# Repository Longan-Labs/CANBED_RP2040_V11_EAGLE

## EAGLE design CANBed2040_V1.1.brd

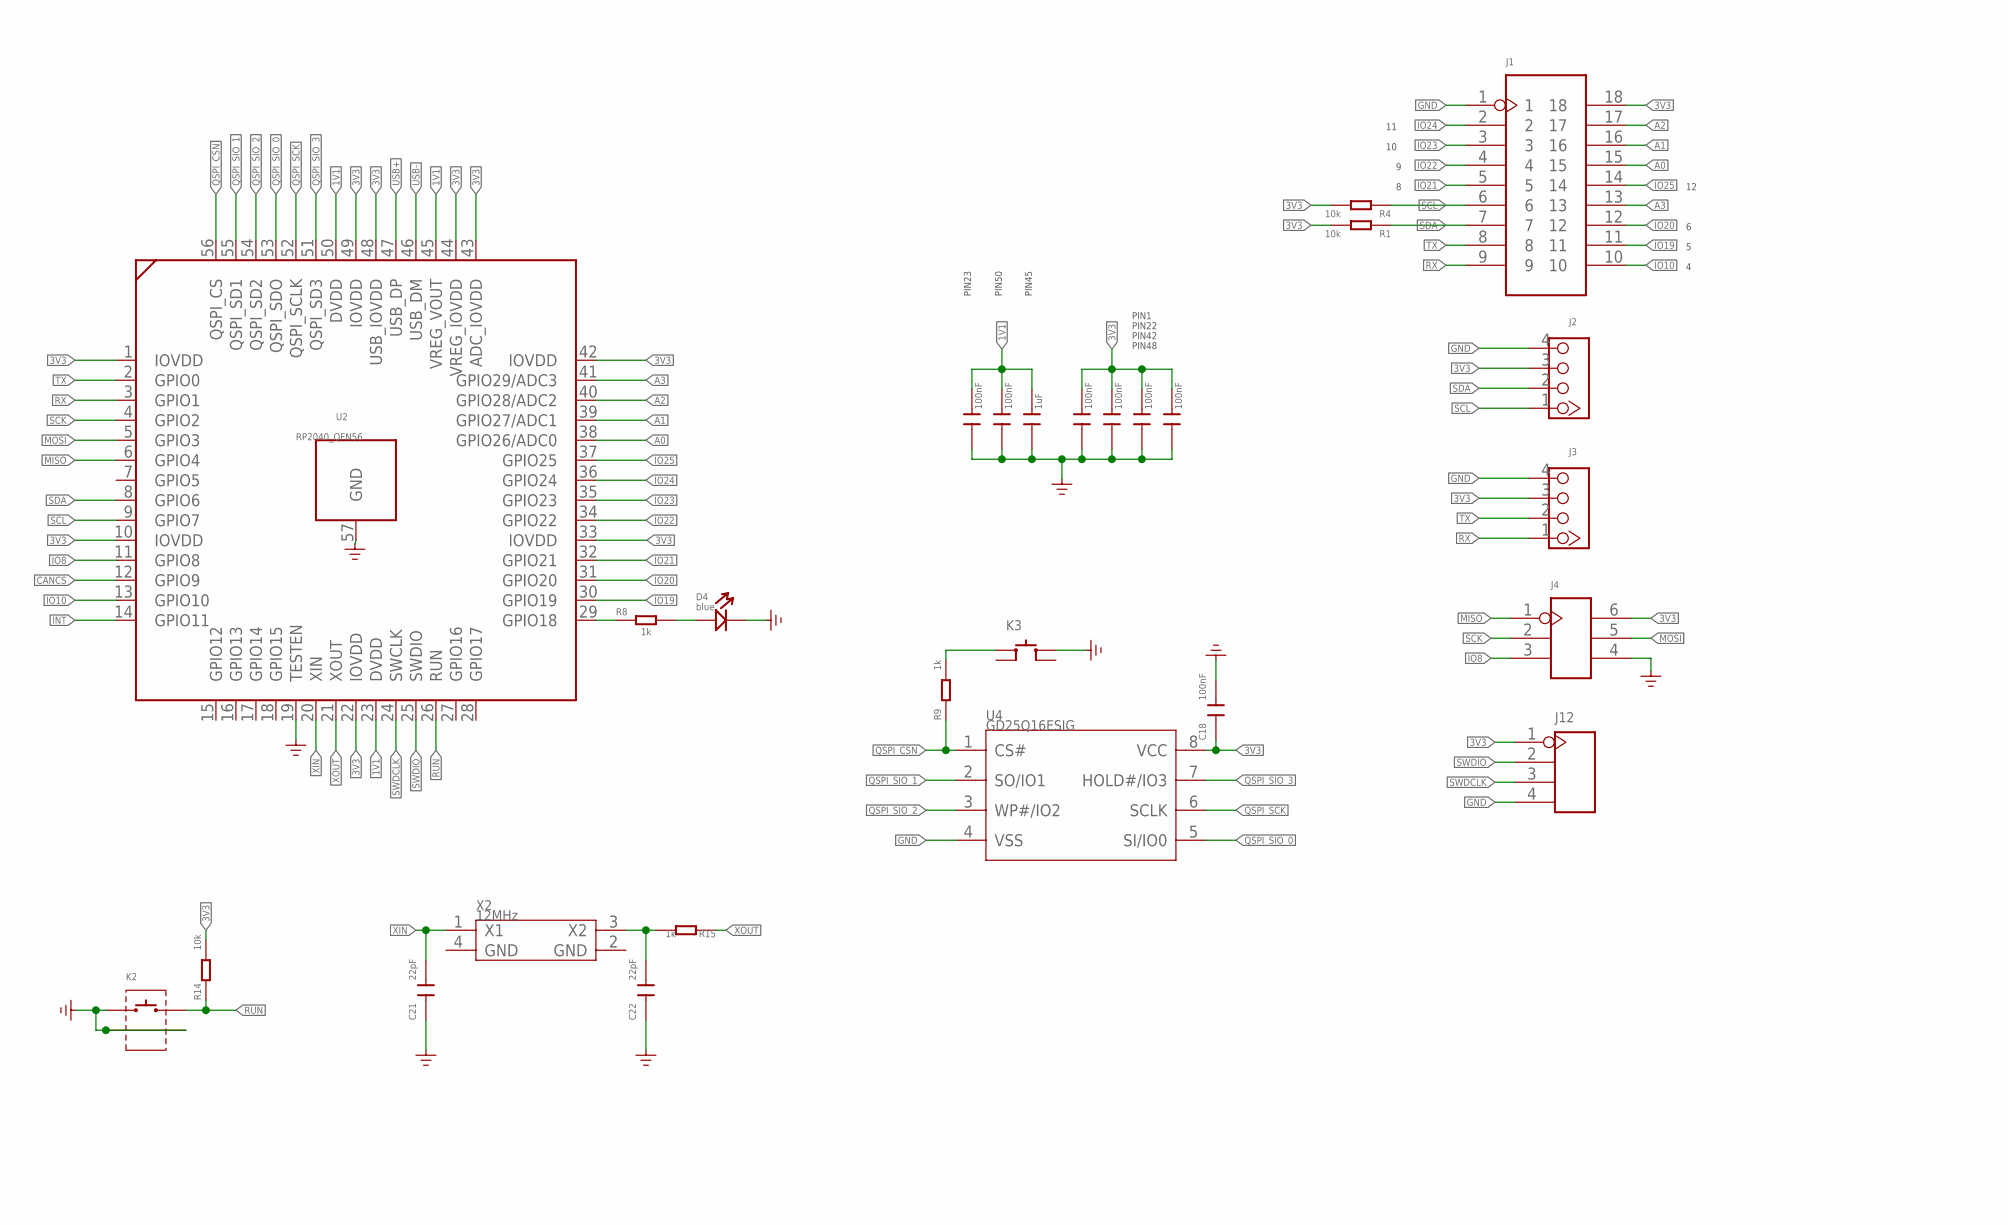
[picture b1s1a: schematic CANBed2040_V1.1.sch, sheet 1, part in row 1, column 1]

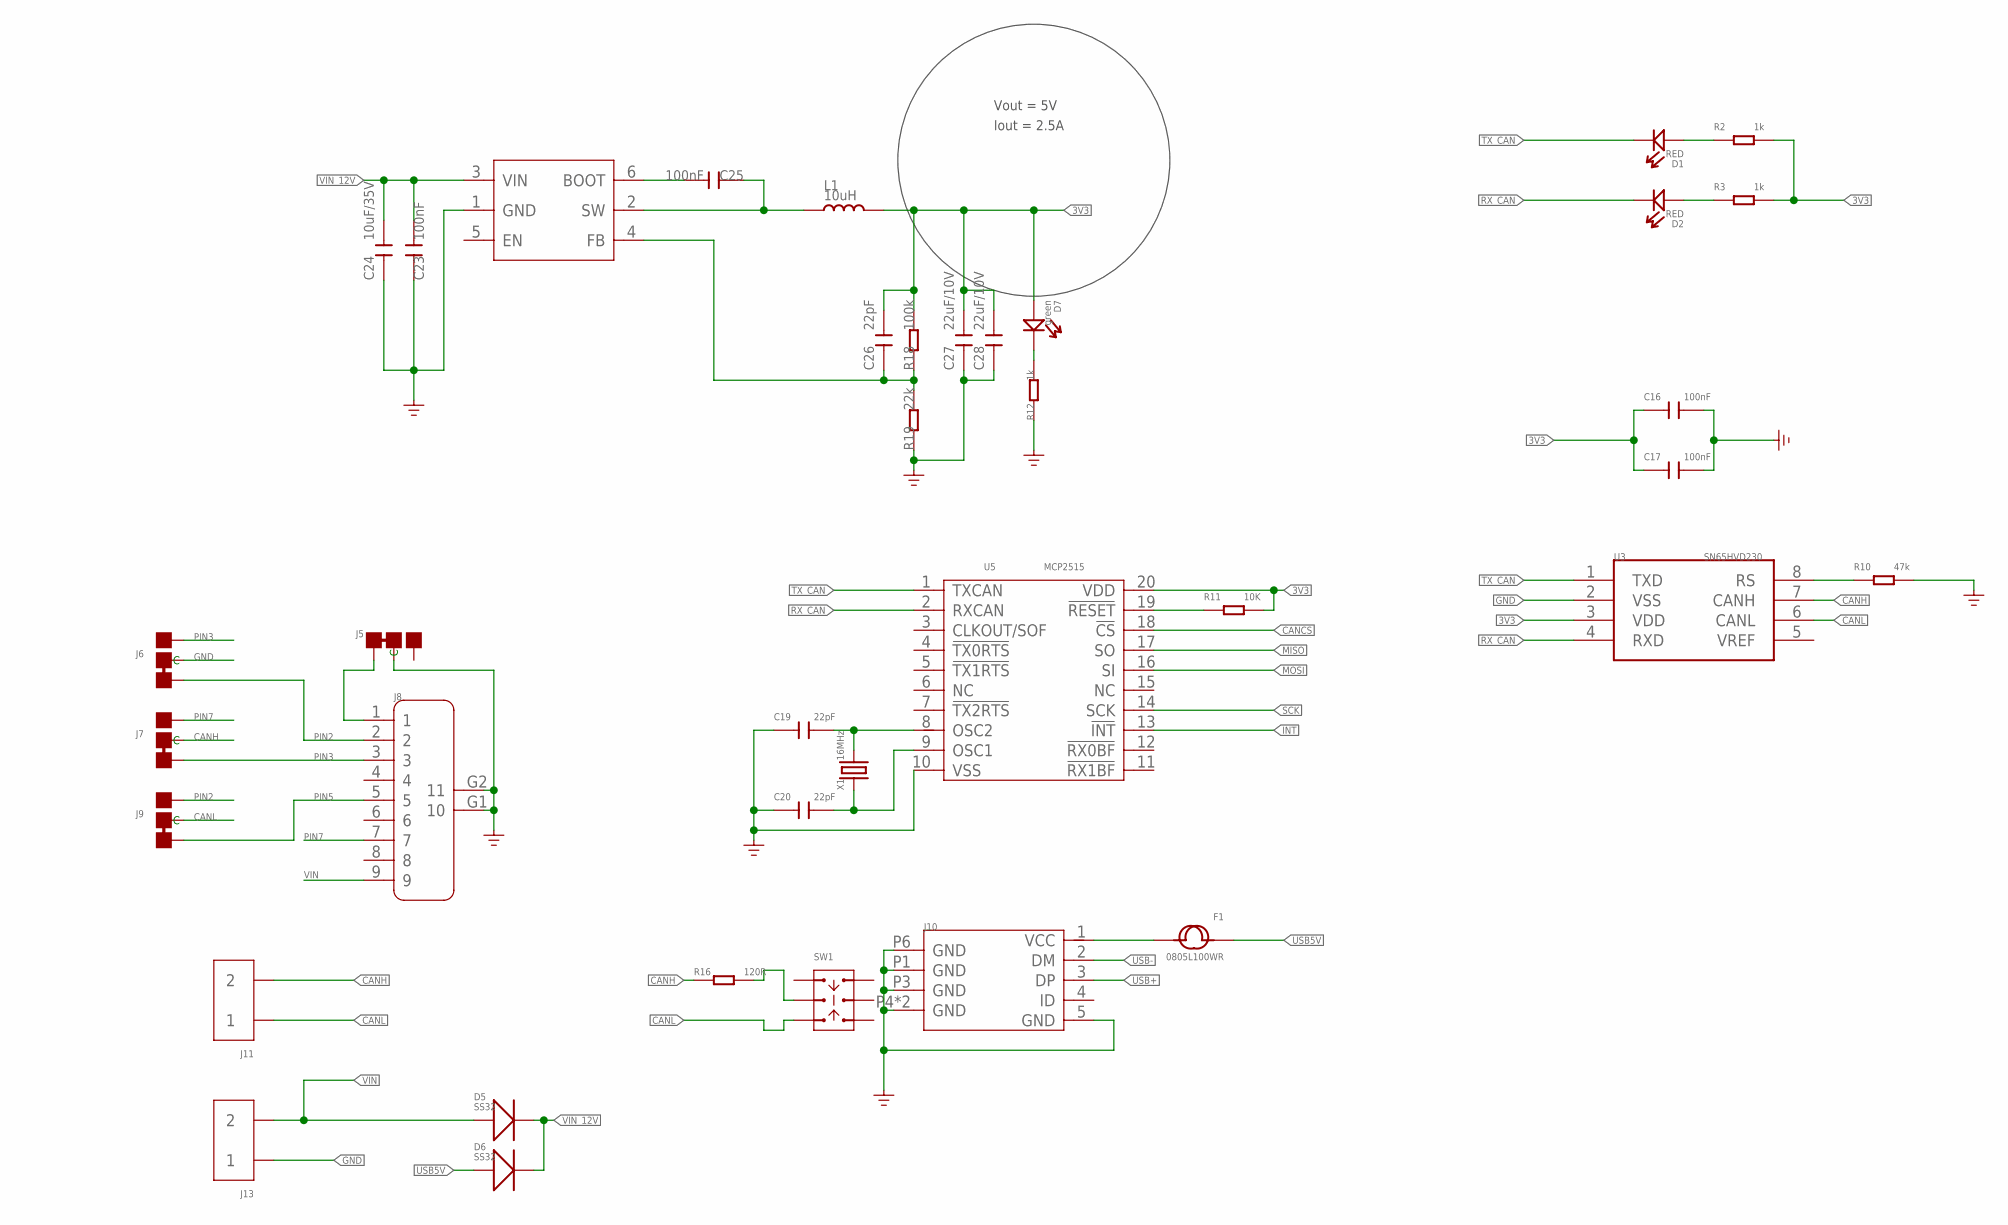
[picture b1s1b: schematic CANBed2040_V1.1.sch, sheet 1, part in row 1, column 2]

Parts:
C9, C10, C12, C13, C14, C15, C16, C17, C18, C23, C25: 100nF; C0603
C11: 1uF; C0603
C19, C20, C21, C22, C26: 22pF; C0603
C24: 10uF/35V; C1206
C27, C28: 22uF/10V; C0805
D1, D2: RED; LED-0603
D4: blue; LED-0603
D5, D6: SS32; DO-214AC
D7: green; LED-0603
F1: 0805L100WR; F0805
J1: HEADER-2X9P-2.54; H2X9-2.54
J2, J3: 320110033; HW4-2.0
J4: HEADER-2X3P-2.54; H2X3-2.54
J5, J6, J7, J9: JUMPER-3P-SHORT; 3P-SMD-SHORT
J8: DB9'MEAL'; DB9-MEAL
J10: MICRO-USB5+4P-320010050; MICRO-USB5+5P-SMD-0.65-7.2X5.06MM
J11, J13: SCREW-TERMINAL-2P'5.08'; H2-5.0-10.5X8.0MM
J12: HEADER-4P-65/35MIL; H4-2.54
K2: BUTTON-2+2P; SW2+2P-7.7X2.75X3.95MM
K3: BUTTON-4P-4.5X4.5X3.3MM; SW4-4.5X4.5X3.3MM
L1: 10uH; L0420
R1, R4, R14: 10k; R0603
R2, R3, R8, R9, R12, R15: 1k; R0603
R10: 47k; R0603
R11: 10K; R0603
R16: 120R; R0603
R18: 100k; R0603
R19: 22k; R0603
SW1: SWITCH-2CH-6P-311010004; SW6-2.54-9.0X3.5X3.2+2.0MM
U2: RP2040_QFN56
U3: SN65HVD230; SOIC8-6.0
U4: GD25Q16ESIG; SOP8-1.27-5.3X5.25X2MM
U5: MCP2515; TSSOP20-0.65-6.5X4.4MM
U6: PMIC-TPS54302; SOT-23-6
X1: 16MHz; X4-SMD-3.2X2.5X0.7MM
X2: 12MHz; X4-SMD-3.2X2.5X0.7MM

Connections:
1V1: C9.2, C10.2, C11.2, U2.23 (DVDD), U2.45 (VREG_VOUT), U2.50 (DVDD)
3V3: C12.2, C13.2, C14.2, C15.2, C16.1, C17.1, C18.1, C26.2, C27.2, C28.2, D7.+, J1.18, J2.3, J3.3, J4.6, J12.1, L1.2, R1.2, R2.2, R3.2, R4.2, R11.2, R14.2, R18.2, U2.1 (IOVDD), U2.10 (IOVDD), U2.22 (IOVDD), U2.33 (IOVDD), U2.42 (IOVDD), U2.43 (ADC_IOVDD), U2.44 (VREG_IOVDD), U2.48 (USB_IOVDD), U2.49 (IOVDD), U3.3 (VDD), U4.8 (VCC), U5.20 (VDD)
A0: J1.15, U2.38 (GPIO26/ADC0)
A1: J1.16, U2.39 (GPIO27/ADC1)
A2: J1.17, U2.40 (GPIO28/ADC2)
A3: J1.13, U2.41 (GPIO29/ADC3)
CANCS: U2.12 (GPIO9), U5.18 (!CS)
CANH: J7.MM (C), J11.2, R16.1, U3.7 (CANH)
CANL: J9.MM (C), J11.1, SW1.CH1B, U3.6 (CANL)
EXT_PWR: F1.2, J10.1 (VCC)
GND: C9.1, C10.1, C11.1, C12.1, C13.1, C14.1, C15.1, C16.2, C17.2, C18.2, C19.1, C20.1, C21.1, C22.1, C23.1, C24.1, C27.1, C28.1, D4.-, J1.1, J2.4, J3.4, J4.4, J5.MM (C), J6.MM (C), J8.G1 (10), J8.G2 (11), J10.5 (GND), J10.P1 (GND), J10.P3 (GND), J10.P4 (GND), J10.P5 (GND), J10.P6 (GND), J12.4, J13.1, K2.1, K2.S1, K2.S2, K3.3 (B0), R10.2, R12.1, R19.1, U2.19 (TESTEN), U2.57 (GND), U3.2 (VSS), U4.4 (VSS), U5.10 (VSS), U6.1 (GND)
INT: U2.14 (GPIO11), U5.13 (!INT)
IO8: J4.3, U2.11 (GPIO8)
IO10: J1.10, U2.13 (GPIO10)
IO19: J1.11, U2.30 (GPIO19)
IO20: J1.12, U2.31 (GPIO20)
IO21: J1.5, U2.32 (GPIO21)
IO22: J1.4, U2.34 (GPIO22)
IO23: J1.3, U2.35 (GPIO23)
IO24: J1.2, U2.36 (GPIO24)
IO25: J1.14, U2.37 (GPIO25)
MISO: J4.1, U2.6 (GPIO4), U5.17 (SO)
MOSI: J4.5, U2.5 (GPIO3), U5.16 (SI)
unnamed: D1.+, R2.1
unnamed: R8.1, U2.29 (GPIO18)
unnamed: R16.2, SW1.COM1
unnamed: D4.+, R8.2
unnamed: K3.1 (A0), R9.2
unnamed: C22.2, R15.2, X2.3 (X2)
unnamed: D7.-, R12.2
unnamed: C25.1, L1.1, U6.2 (SW)
unnamed: J5.11 (L), J8.1
unnamed: C25.2, U6.6 (BOOT)
unnamed: D2.+, R3.1
unnamed: C19.2, U5.8 (OSC2), X1.3 (2)
unnamed: C20.2, U5.9 (OSC1), X1.1
unnamed: R10.1, U3.8 (RS)
unnamed: C26.1, R18.1, R19.2, U6.4 (FB)
PIN2: J6.11 (L), J8.2, J9.00 (R)
PIN3: J6.00 (R), J7.11 (L), J8.3
PIN5: J8.5, J9.11 (L)
PIN7: J7.00 (R), J8.7
QSPI_CSN: R9.1, U2.56 (QSPI_CS), U4.1 (CS#)
QSPI_SCK: U2.52 (QSPI_SCLK), U4.6 (SCLK)
QSPI_SIO_0: U2.53 (QSPI_SDO), U4.5 (SI/IO0)
QSPI_SIO_1: U2.55 (QSPI_SD1), U4.2 (SO/IO1)
QSPI_SIO_2: U2.54 (QSPI_SD2), U4.3 (WP#/IO2)
QSPI_SIO_3: U2.51 (QSPI_SD3), U4.7 (HOLD#/IO3)
RST_N: R11.1, U5.19 (!RESET)
RUN: K2.2, R14.1, U2.26 (RUN)
RX: J1.9, J3.1, U2.3 (GPIO1)
RX_CAN: D2.-, U3.4 (RXD), U5.2 (RXCAN)
SCK: J4.2, U2.4 (GPIO2), U5.14 (SCK)
SCL: J1.6, J2.1, R4.1, U2.9 (GPIO7)
SDA: J1.7, J2.2, R1.1, U2.8 (GPIO6)
SWDCLK: J12.3, U2.24 (SWCLK)
SWDIO: J12.2, U2.25 (SWDIO)
TX: J1.8, J3.2, U2.2 (GPIO0)
TX_CAN: D1.-, U3.1 (TXD), U5.1 (TXCAN)
USB5V: D6.1 (+), F1.1
USB+: J10.3 (DP), U2.47 (USB_DP)
USB-: J10.2 (DM), U2.46 (USB_DM)
VIN: D5.1 (+), J8.9, J13.2
VIN_12V: C23.2, C24.2, D5.2 (-), D6.2 (-), U6.3 (VIN)
XIN: C21.2, U2.20 (XIN), X2.1 (X1)
XOUT: R15.1, U2.21 (XOUT)

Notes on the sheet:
PIN1
PIN22
PIN42
PIN48
PIN23
PIN50
PIN45
Vout = 5V
Iout = 2.5A

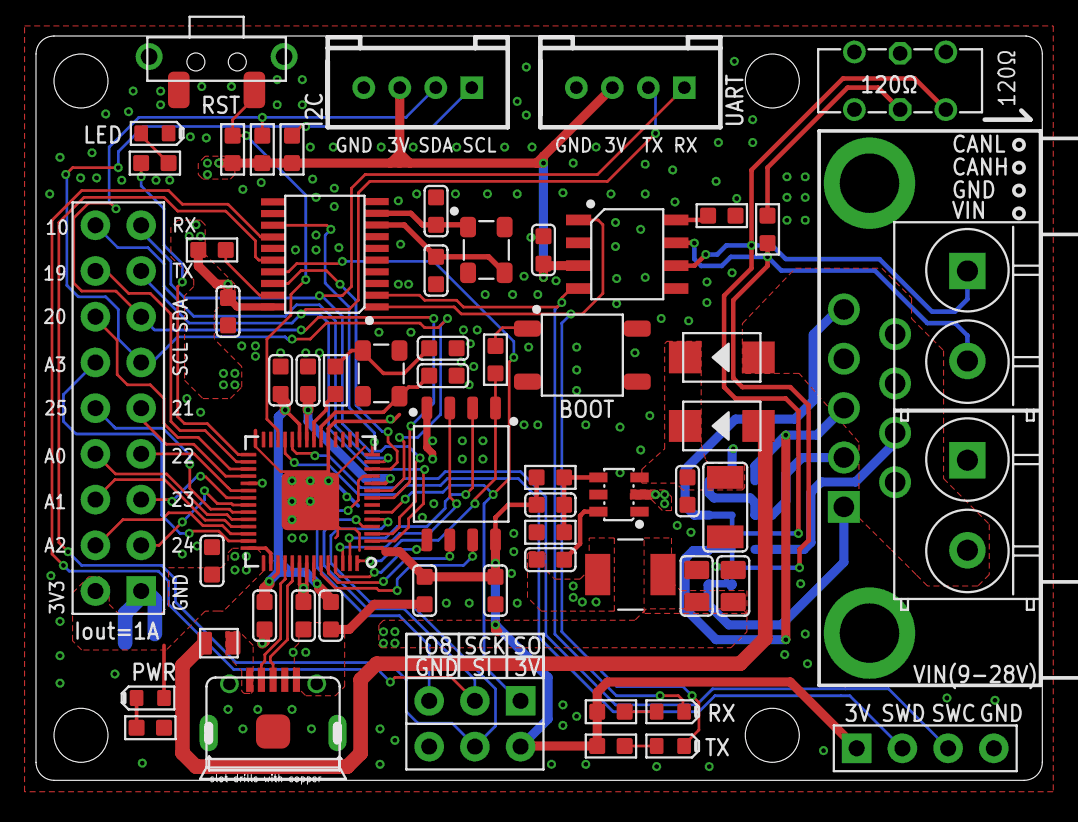
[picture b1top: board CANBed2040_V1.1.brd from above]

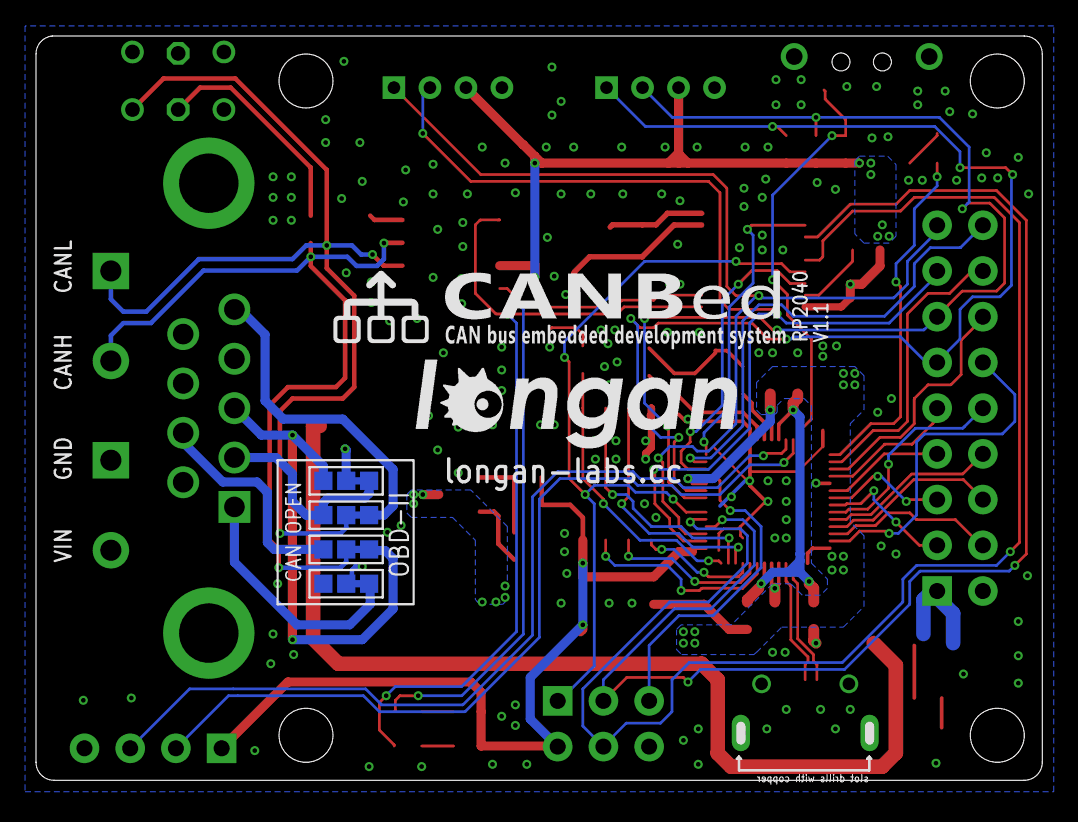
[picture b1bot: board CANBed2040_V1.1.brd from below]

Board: 2 copper layers, 55.4 x 41.2 mm, 66 parts (5 on the bottom side), 66 nets.

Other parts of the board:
U$12: LONGAN-SILK-SMALL
